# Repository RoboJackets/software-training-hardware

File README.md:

# software-training-hardware
Repository to contain all eagle files and any other electrical or mechanical files for the software training platform.

# Pin Mapping

| Pin | Type  In Actual | Type out actual | Notes |
|-|-|-|-|
| A0 | digital | PWM | |
| A1 | digital | PWM | |
| A2 | analog  | Na | |
| A3 | analog  | Na | |
| A4 | analog  | Na | |
| A5 | digital | PWM | |
| 13 | digital  | PWM | |
| 12 | Na  | Na | do not use |
| 27 | digital  | PWM | |
| 33 | analog   | PWM | |
| 15 | digital  | PWM | |
| 32 | analog   | PWM | |
| 14 | digital  | PWM | |

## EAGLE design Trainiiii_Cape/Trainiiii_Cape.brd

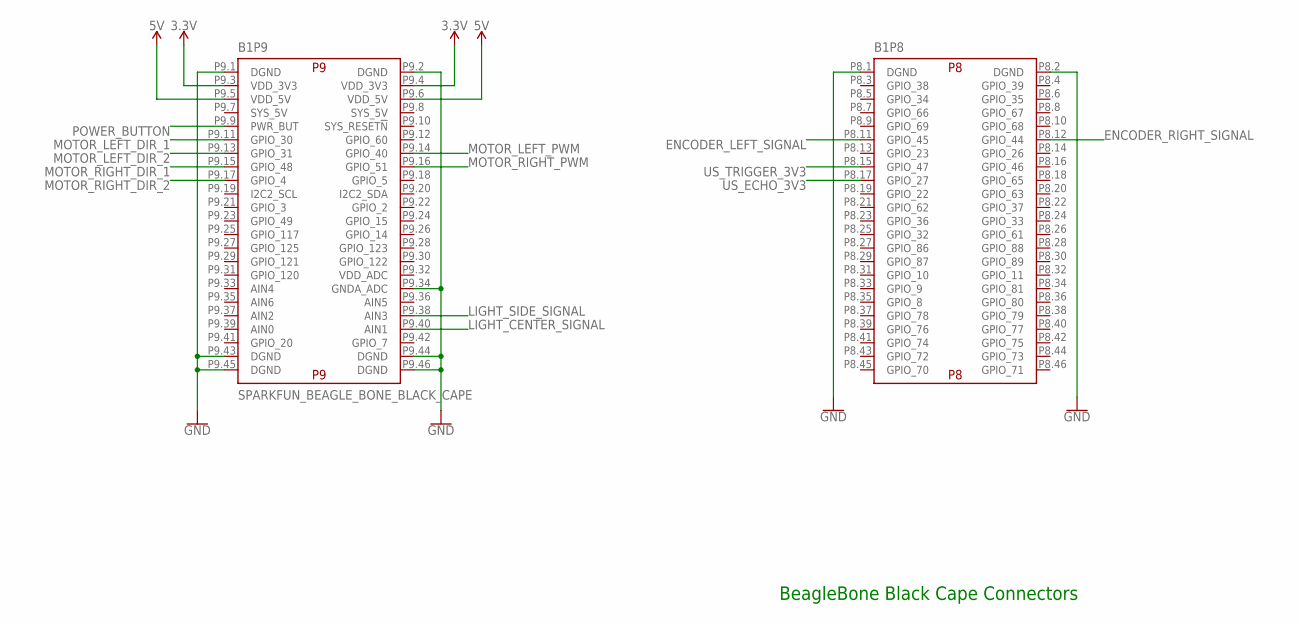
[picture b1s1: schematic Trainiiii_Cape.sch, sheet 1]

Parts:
B1: SPARKFUN_BEAGLE_BONE_BLACK_CAPE; BEAGLE_BONE_BLACK_CAPE

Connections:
3.3V: B1.P9.3 (VDD_3V3), B1.P9.4 (VDD_3V3); also elsewhere on the board
5V: B1.P9.5 (VDD_5V), B1.P9.6 (VDD_5V); also elsewhere on the board
ENCODER_LEFT_SIGNAL: B1.P8.11 (GPIO_45); also elsewhere on the board
ENCODER_RIGHT_SIGNAL: B1.P8.12 (GPIO_44); also elsewhere on the board
GND: B1.P8.1 (DGND), B1.P8.2 (DGND), B1.P9.1 (DGND), B1.P9.2 (DGND), B1.P9.34 (GNDA_ADC), B1.P9.43 (DGND), B1.P9.44 (DGND), B1.P9.45 (DGND), B1.P9.46 (DGND); also elsewhere on the board
LIGHT_CENTER_SIGNAL: B1.P9.40 (AIN1); also elsewhere on the board
LIGHT_SIDE_SIGNAL: B1.P9.38 (AIN3); also elsewhere on the board
MOTOR_LEFT_DIR_1: B1.P9.11 (GPIO_30); also elsewhere on the board
MOTOR_LEFT_DIR_2: B1.P9.13 (GPIO_31); also elsewhere on the board
MOTOR_LEFT_PWM: B1.P9.14 (GPIO_40); also elsewhere on the board
MOTOR_RIGHT_DIR_1: B1.P9.15 (GPIO_48); also elsewhere on the board
MOTOR_RIGHT_DIR_2: B1.P9.17 (GPIO_4); also elsewhere on the board
MOTOR_RIGHT_PWM: B1.P9.16 (GPIO_51); also elsewhere on the board
POWER_BUTTON: B1.P9.9 (PWR_BUT); also elsewhere on the board
US_ECHO_3V3: B1.P8.17 (GPIO_27); also elsewhere on the board
US_TRIGGER_3V3: B1.P8.15 (GPIO_47); also elsewhere on the board

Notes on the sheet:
BeagleBone Black Cape Connectors

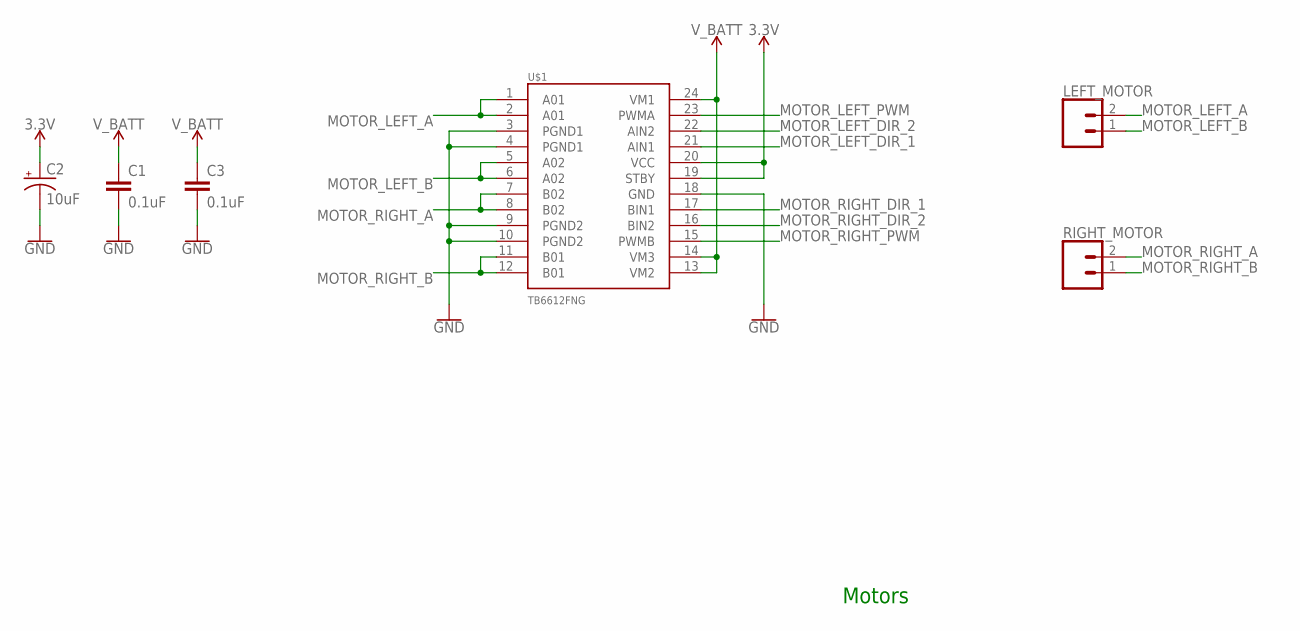
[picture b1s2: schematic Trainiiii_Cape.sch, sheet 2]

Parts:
C1, C3: 0.1uF; 0402
C2: 10uF; EIA3528
LEFT_MOTOR: CONN_02; 1X02
RIGHT_MOTOR: CONN_02; 1X02
U$1: TB6612FNG; SSOP24

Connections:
3.3V: C2.A (+), U$1.19 (STBY), U$1.20 (VCC); also elsewhere on the board
GND: C1.2, C2.C (-), C3.2, U$1.3 (PGND1), U$1.4 (PGND1), U$1.9 (PGND2), U$1.10 (PGND2), U$1.18 (GND); also elsewhere on the board
MOTOR_LEFT_A: LEFT_MOTOR.2, U$1.1 (A01), U$1.2 (A01)
MOTOR_LEFT_B: LEFT_MOTOR.1, U$1.5 (A02), U$1.6 (A02)
MOTOR_LEFT_DIR_1: U$1.21 (AIN1); also elsewhere on the board
MOTOR_LEFT_DIR_2: U$1.22 (AIN2); also elsewhere on the board
MOTOR_LEFT_PWM: U$1.23 (PWMA); also elsewhere on the board
MOTOR_RIGHT_A: RIGHT_MOTOR.2, U$1.7 (B02), U$1.8 (B02)
MOTOR_RIGHT_B: RIGHT_MOTOR.1, U$1.11 (B01), U$1.12 (B01)
MOTOR_RIGHT_DIR_1: U$1.17 (BIN1); also elsewhere on the board
MOTOR_RIGHT_DIR_2: U$1.16 (BIN2); also elsewhere on the board
MOTOR_RIGHT_PWM: U$1.15 (PWMB); also elsewhere on the board
V_BATT: C1.1, C3.1, U$1.13 (VM2), U$1.14 (VM3), U$1.24 (VM1); also elsewhere on the board

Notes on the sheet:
Motors

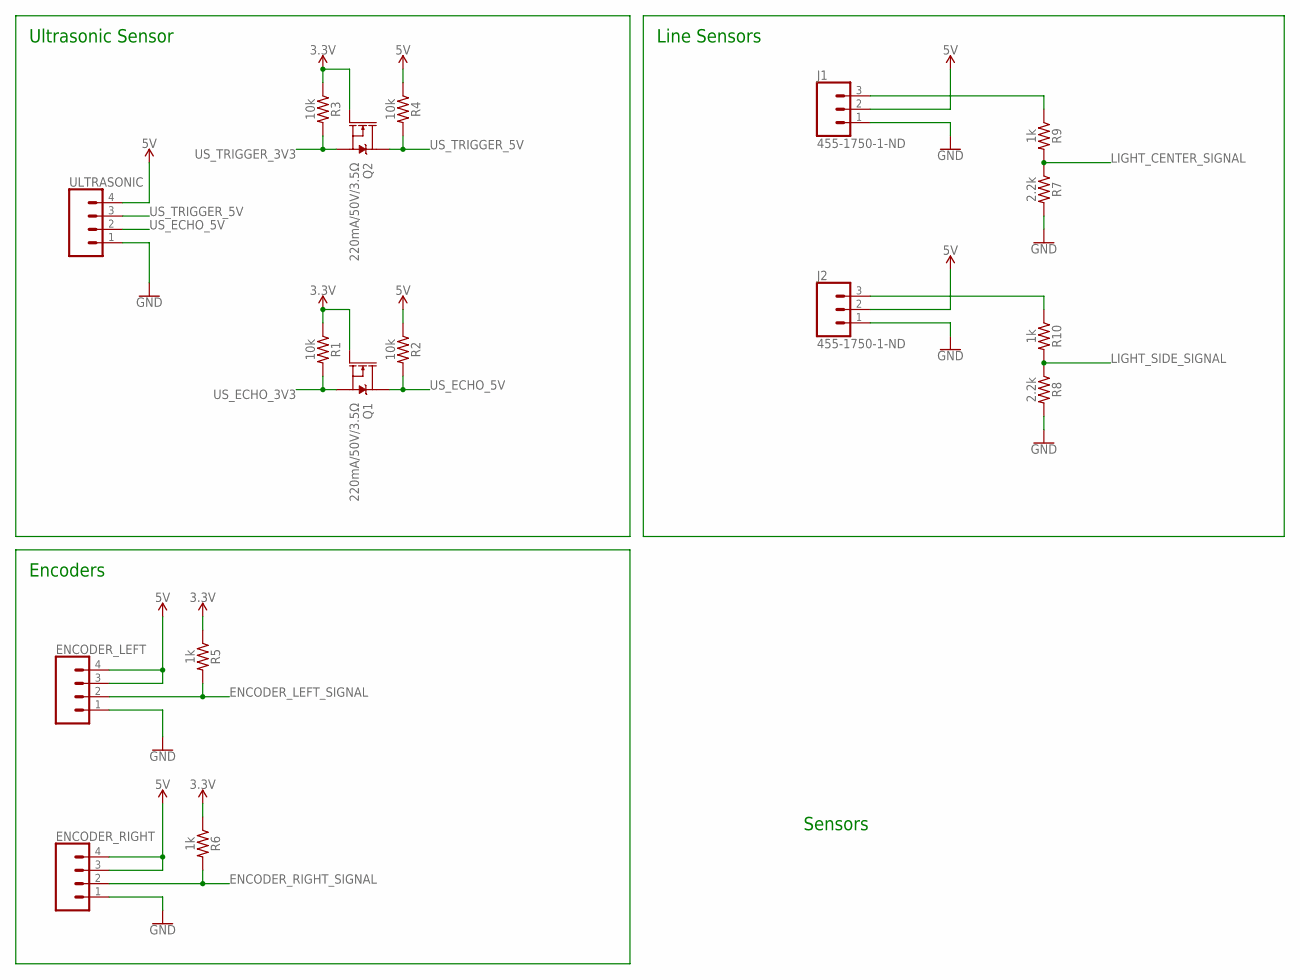
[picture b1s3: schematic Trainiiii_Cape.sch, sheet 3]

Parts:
ENCODER_LEFT: CONN_04PTH; 1X04
ENCODER_RIGHT: CONN_04PTH; 1X04
J1, J2: 455-1750-1-ND; 1X03
Q1, Q2: 220mA/50V/3.5Ω; SOT23-3
R1, R2, R3, R4: 10k; 0603
R5, R6, R9, R10: 1k; 0603
R7, R8: 2.2k; 0603
ULTRASONIC: CONN_04PTH; 1X04

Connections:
3.3V: Q1.1 (G), Q2.1 (G), R1.1, R3.1, R5.1, R6.1; also elsewhere on the board
5V: ENCODER_LEFT.3, ENCODER_LEFT.4, ENCODER_RIGHT.3, ENCODER_RIGHT.4, J1.2, J2.2, R2.1, R4.1, ULTRASONIC.4; also elsewhere on the board
ENCODER_LEFT_SIGNAL: ENCODER_LEFT.2, R5.2; also elsewhere on the board
ENCODER_RIGHT_SIGNAL: ENCODER_RIGHT.2, R6.2; also elsewhere on the board
GND: ENCODER_LEFT.1, ENCODER_RIGHT.1, J1.1, J2.1, R7.2, R8.2, ULTRASONIC.1; also elsewhere on the board
LIGHT_CENTER_SIGNAL: R7.1, R9.2; also elsewhere on the board
LIGHT_SIDE_SIGNAL: R8.1, R10.2; also elsewhere on the board
unnamed: J2.3, R10.1
unnamed: J1.3, R9.1
US_ECHO_3V3: Q1.2 (S), R1.2; also elsewhere on the board
US_ECHO_5V: Q1.3 (D), R2.2, ULTRASONIC.2
US_TRIGGER_3V3: Q2.2 (S), R3.2; also elsewhere on the board
US_TRIGGER_5V: Q2.3 (D), R4.2, ULTRASONIC.3

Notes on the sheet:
Ultrasonic Sensor
Line Sensors
Encoders
Sensors

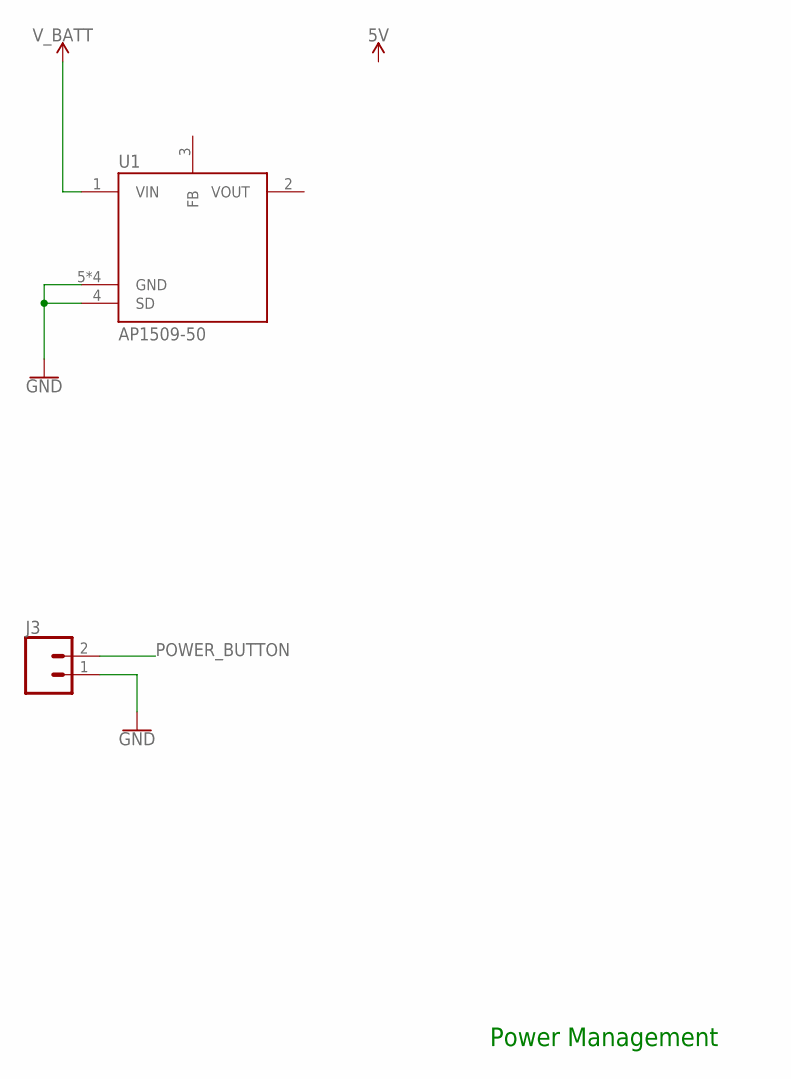
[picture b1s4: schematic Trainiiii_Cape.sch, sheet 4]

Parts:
J3: CONN_02; 1X02
U1: AP1509-50; SOIC-8

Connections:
GND: J3.1, U1.4 (SD), U1.5 (GND), U1.6 (GND), U1.7 (GND), U1.8 (GND); also elsewhere on the board
POWER_BUTTON: J3.2; also elsewhere on the board
V_BATT: U1.1 (VIN); also elsewhere on the board

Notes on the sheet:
Power Management

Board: 2 copper layers, 26 parts (0 on the bottom side), 25 nets, no tracks yet.

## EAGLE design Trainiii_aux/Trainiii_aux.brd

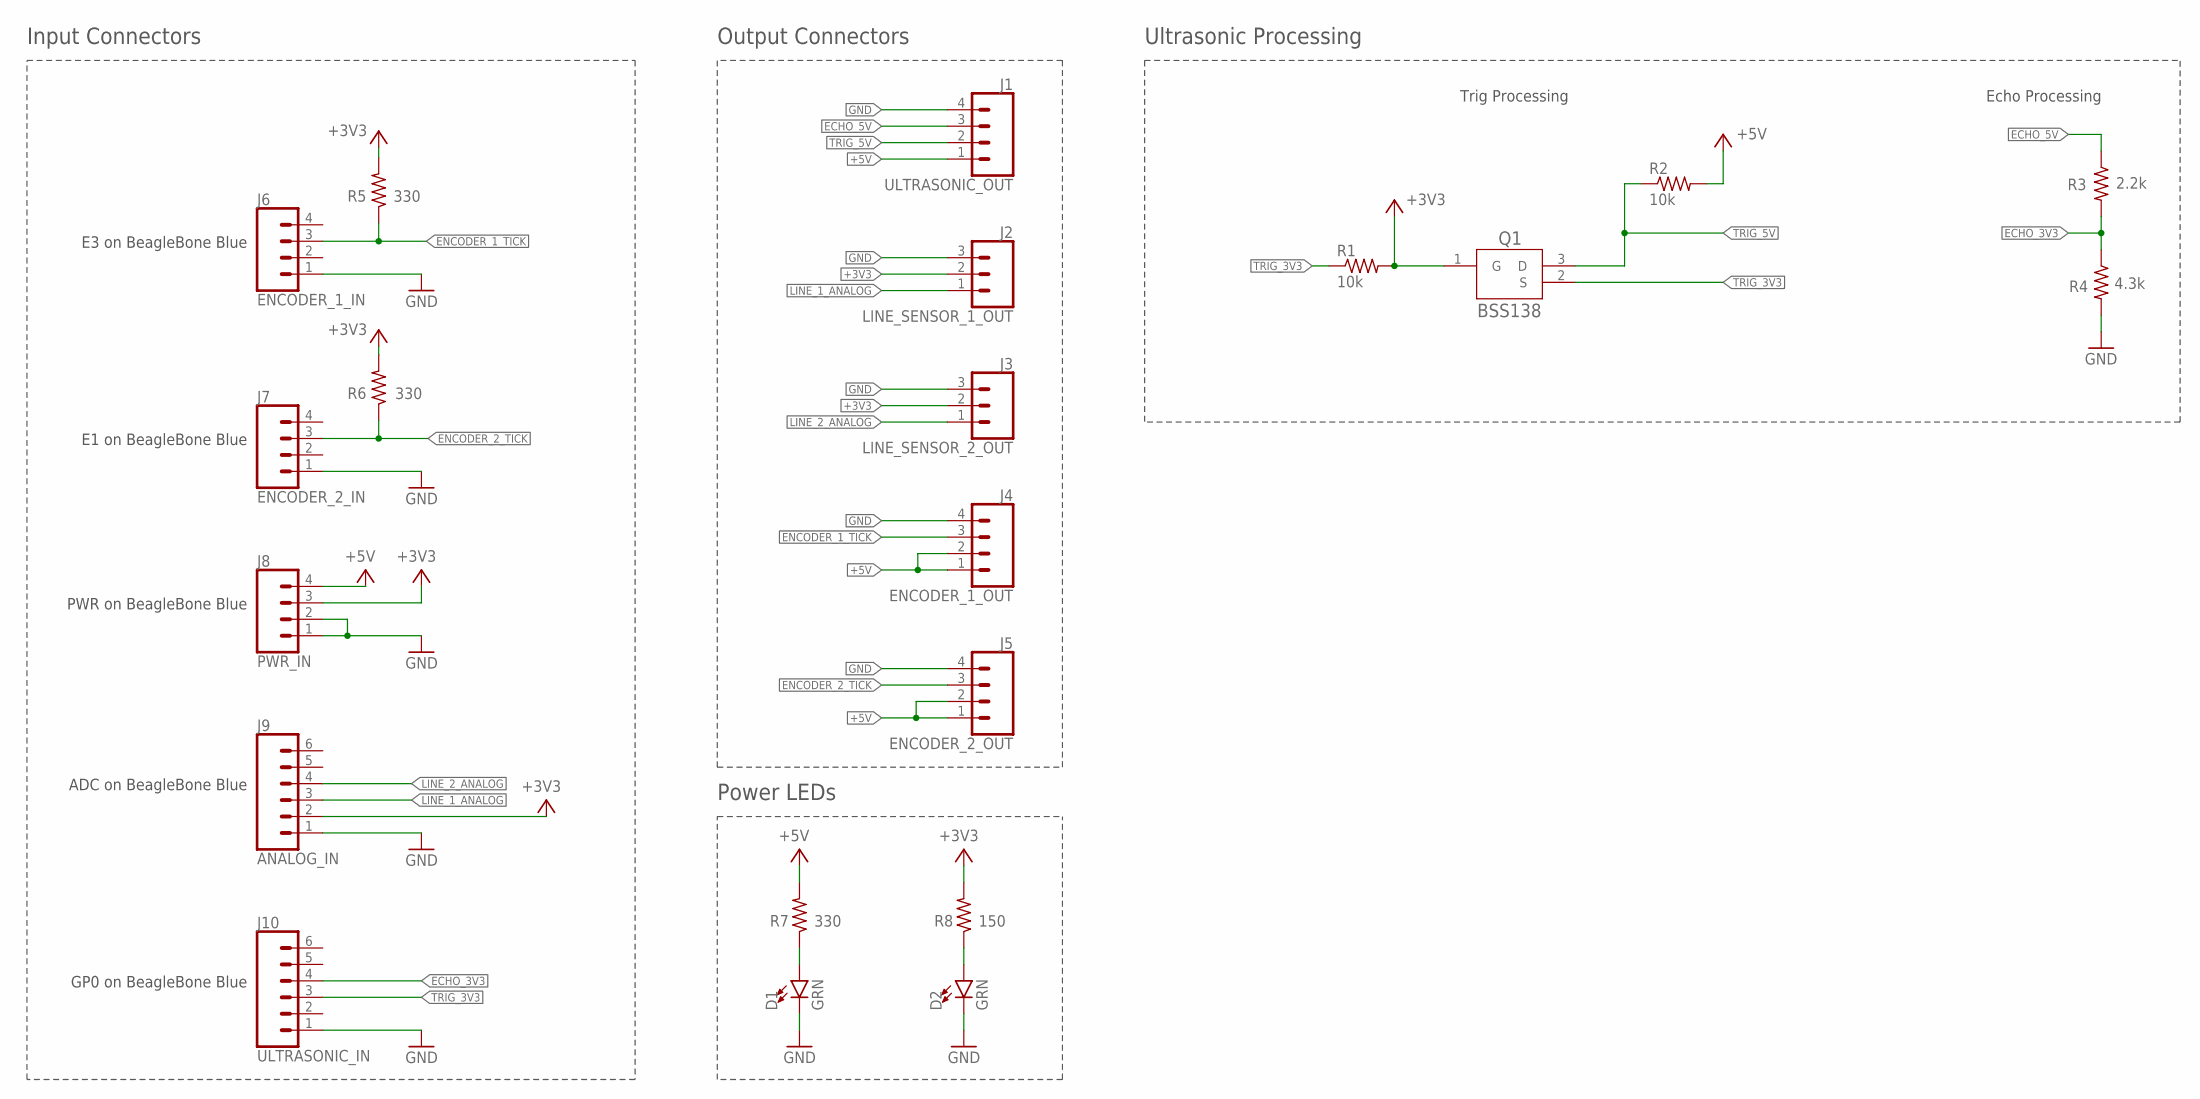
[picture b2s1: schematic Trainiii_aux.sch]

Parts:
D1, D2: GRN; LED-0603
J1: ULTRASONIC_OUT; 1X04
J2: LINE_SENSOR_1_OUT; 1X03
J3: LINE_SENSOR_2_OUT; 1X03
J4: ENCODER_1_OUT; 1X04
J5: ENCODER_2_OUT; 1X04
J6: ENCODER_1_IN; 1X04
J7: ENCODER_2_IN; 1X04
J8: PWR_IN; 1X04
J9: ANALOG_IN; 1X06
J10: ULTRASONIC_IN; 1X06
Q1: BSS138; SOT-23-3L
R1, R2: 10k; R0603
R3: 2.2k; R0603
R4: 4.3k; R0603
R5, R6, R7: 330; R0603
R8: 150; R0603

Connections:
3V3_LED: D2.A, R8.1
5V_LED: D1.A, R7.1
+3V3: J2.2, J3.2, J8.3, J9.2, Q1.1 (G), R1.2, R5.2, R6.2, R8.2
+5V: J1.1, J4.1, J4.2, J5.1, J5.2, J8.4, R2.2, R7.2
ECHO_3V3: J10.4, R3.2, R4.1
ECHO_5V: J1.3, R3.1
ENCODER_1_TICK: J4.3, J6.3, R5.1
ENCODER_2_TICK: J5.3, J7.3, R6.1
GND: D1.C, D2.C, J1.4, J2.3, J3.3, J4.4, J5.4, J6.1, J7.1, J8.1, J8.2, J9.1, J10.1, R4.2
LINE_1_ANALOG: J2.1, J9.3
LINE_2_ANALOG: J3.1, J9.4
TRIG_3V3: J10.3, Q1.2 (S), R1.1
TRIG_5V: J1.2, Q1.3 (D), R2.1

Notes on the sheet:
Output Connectors
Ultrasonic Processing
Trig Processing
Echo Processing
E1 on BeagleBone Blue
E3 on BeagleBone Blue
PWR on BeagleBone Blue
ADC on BeagleBone Blue
GP0 on BeagleBone Blue
Input Connectors
Power LEDs

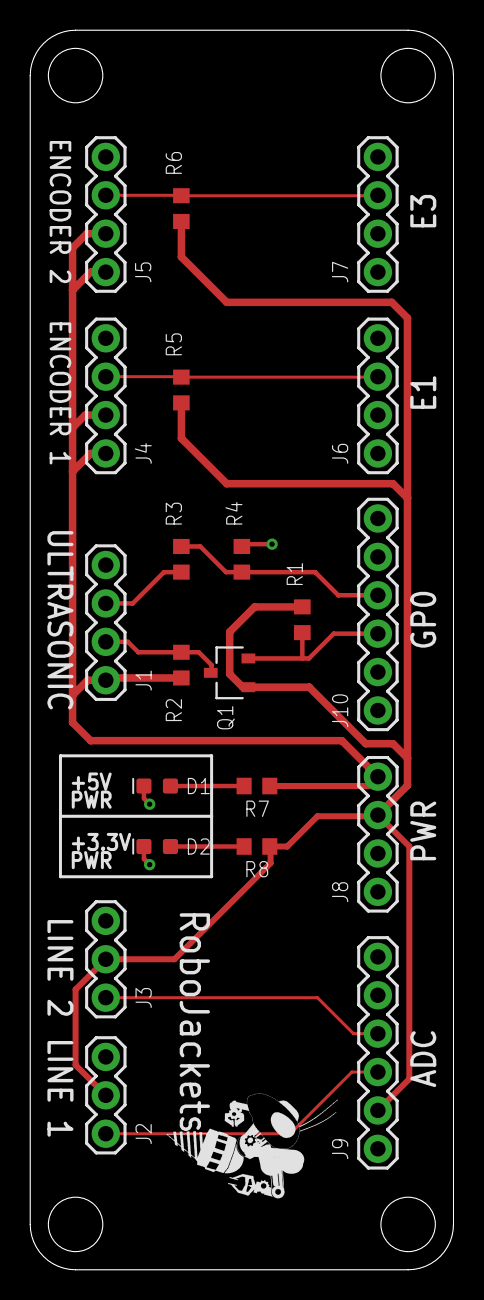
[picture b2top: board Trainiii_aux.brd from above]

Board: 2 copper layers, 28.0 x 82.0 mm, 22 parts (0 on the bottom side), 13 nets.

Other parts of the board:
U$1: ROBOBUZZ_0.6X

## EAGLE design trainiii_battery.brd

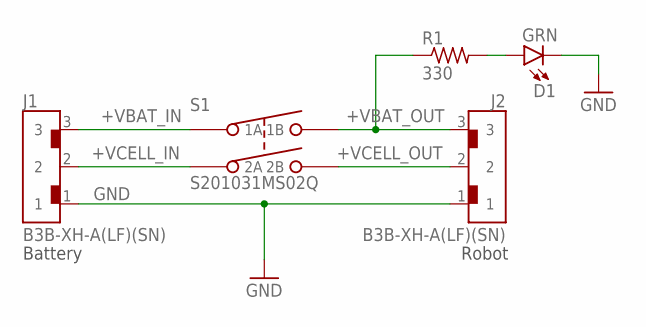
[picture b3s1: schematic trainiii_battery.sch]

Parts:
D1: GRN; LED-0603
J1, J2: B3B-XH-A(LF)(SN)
R1: 330; R0603
S1: S201031MS02Q; S201

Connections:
+VBAT_IN: J1.3, S1.1 (1A)
+VBAT_OUT: J2.3, R1.1, S1.2 (1B)
+VCELL_IN: J1.2, S1.4 (2A)
+VCELL_OUT: J2.2, S1.5 (2B)
GND: D1.C, J1.1, J2.1
LED_IN: D1.A, R1.2

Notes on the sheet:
Battery
Robot

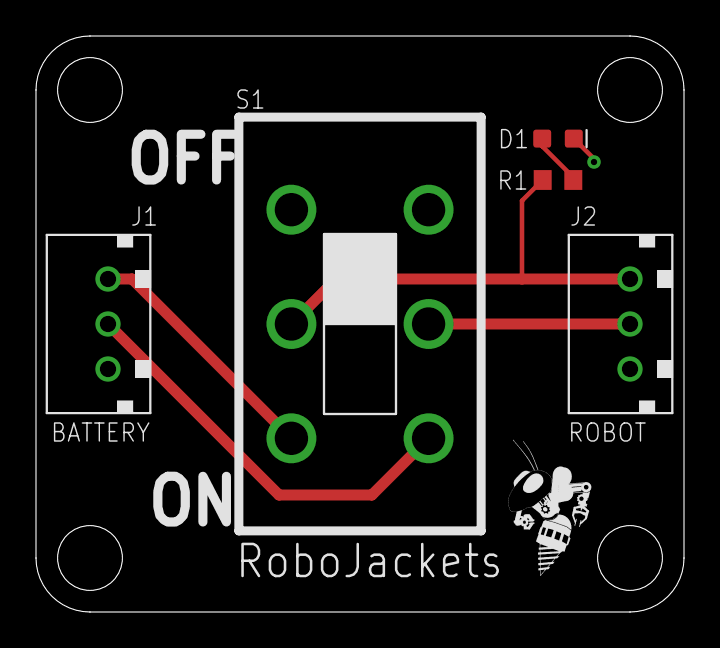
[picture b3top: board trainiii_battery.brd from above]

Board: 2 copper layers, 36.0 x 32.0 mm, 6 parts (0 on the bottom side), 6 nets.

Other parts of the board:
U$2: ROBOBUZZ_0.4X

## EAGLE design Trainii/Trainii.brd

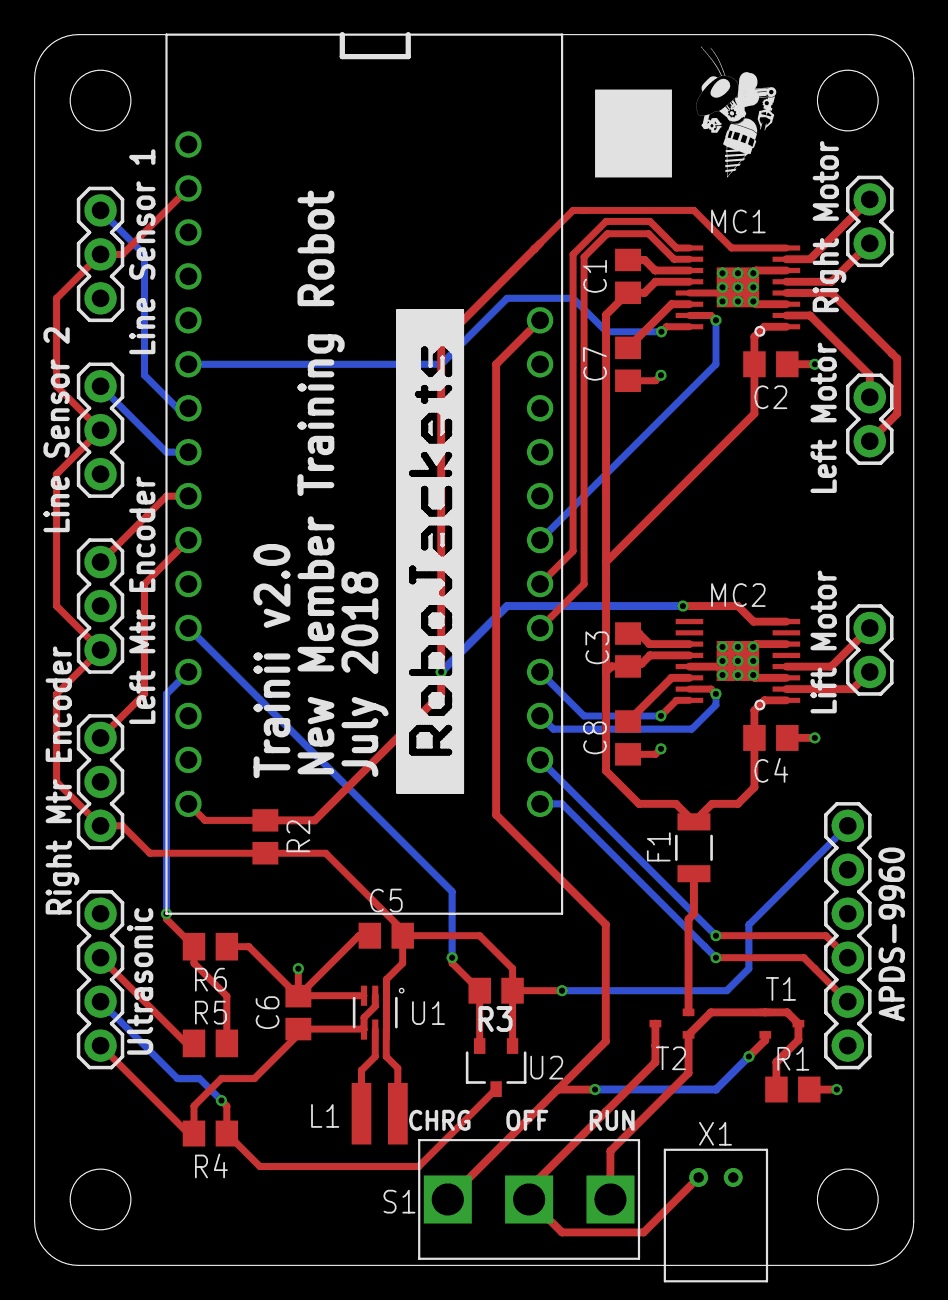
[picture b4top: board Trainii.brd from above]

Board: 2 copper layers, 50.8 x 71.1 mm, 36 parts (0 on the bottom side), 36 nets.

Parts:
C1, C3: 0.01uF; C0805
C2, C4: 10uF; C0805
C5, C6: 10uF 16V; C0805
C7, C8: 2.2uF; C0805
F1: 0ZCJ0100FF2E; 1206
J1: APDS-9960; 1X06
J2: Left Mtr Encoder; 1X03
J3: Right Mtr Encoder; 1X03
J4: Line Sensor 1; 1X03
J5: Line Sensor 2; 1X03
J6: Ultrasonic; 1X04
J7: Left Motor; 1X02
J8: Right Motor; 1X02
J9: Lift Motor; 1X02
L1: 4.7uH; VLS3012HBX
M1: ESP32
MC1, MC2: DRV8833; HTSSOP-16
R1, R2, R3, R4: 10kΩ; R0805
R5: 2k2Ω; M0805
R6: 4k3Ω; M0805
S1: 100SP3T
T1, T2: MCH3383SC-70FL; SOTFL65P210X90-3
U1: TPS61222DCKR; DCK6
U2: BSS138; SOT-23-3L
U$2: ROBOJACKETS
U$6: ROBOBUZZ_0.4X
X1: JST-PH2; JST-PH

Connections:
3V3: C5.1, J1.6, J2.1, J3.1, J4.2, J5.2, L1.1, M1.3V, R2.2, R3.1, U1.1, U1.6, U2.1
+5V: C6.1, J6.1, R4.1, U1.2, U1.4
ECHO_3V3: M1.MI, R5.2, R6.1
ECHO_5V: J6.3, R5.1
GND: C2.2, C4.2, C5.2, C6.2, C7.2, C8.2, J1.4, J2.2, J3.2, J4.1, J5.1, J6.4, M1.GND, MC1.3, MC1.6, MC1.13, MC1.17, MC2.3, MC2.6, MC2.13, MC2.17, R1.1, R6.2, U1.3, X1.1
LEFT_0: J7.1, MC1.2
LEFT_1: J7.2, MC1.4
LEFT_A: M1.A1, MC1.16
LEFT_B: M1.A10, MC1.15
LIFT_0: J9.1, MC2.2
LIFT_1: J9.2, MC2.4
LIFT_A: M1.A7, MC2.16
LIFT_B: M1.A6, MC2.15
LINE_OUT_1: J4.3, M1.A2
LINE_OUT_2: J5.3, M1.A3
MOTOR_FAULT: M1.21, MC1.8, MC2.8, R2.1
unnamed: L1.2, U1.5
unnamed: R1.2, S1.3, T1.1, T1.3, T2.1
unnamed: C8.1, MC2.14
unnamed: C1.1, MC1.11
unnamed: C7.1, MC1.14
unnamed: C3.1, MC2.11
RIGHT_0: J8.1, MC1.7
RIGHT_1: J8.2, MC1.5
RIGHT_A: M1.A9, MC1.9
RIGHT_B: M1.A8, MC1.10
SCL: J1.3, M1.22
SDA: J1.2, M1.23
TICK_LEFT: J2.3, M1.A4
TICK_RIGHT: J3.3, M1.A5
TRIG_3V3: M1.MO, R3.2, U2.2
TRIG_5V: J6.2, R4.2, U2.3
VBAT: S1.2, T2.3, X1.2
VBAT_HUZZAH: M1.BAT, S1.1, T1.2
VBAT_MOTOR: F1.1, T2.2
VBAT_MOTOR_FUSE: C1.2, C2.1, C3.2, C4.1, F1.2, MC1.1, MC1.12, MC2.1, MC2.12

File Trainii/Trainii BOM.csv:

"Part";"Value";"Device";"Package";"Description";"MANUFACTURER_PART_NUMBER";"PROD_ID";"SPICEPREFIX";"VENDOR";
"C1";"0.01uF";"C-USC0805";"C0805";"CAPACITOR, American symbol";"";"";"C";"";
"C2";"10uF";"C-USC0805";"C0805";"CAPACITOR, American symbol";"";"";"C";"";
"C3";"0.01uF";"C-USC0805";"C0805";"CAPACITOR, American symbol";"";"";"C";"";
"C4";"10uF";"C-USC0805";"C0805";"CAPACITOR, American symbol";"";"";"C";"";
"C5";"10uF 16V";"C-USC0805";"C0805";"CAPACITOR, American symbol";"";"";"C";"";
"C6";"10uF 16V";"C-USC0805";"C0805";"CAPACITOR, American symbol";"";"";"C";"";
"C7";"2.2uF";"C-USC0805";"C0805";"CAPACITOR, American symbol";"";"";"C";"";
"C8";"2.2uF";"C-USC0805";"C0805";"CAPACITOR, American symbol";"";"";"C";"";
"F1";"0ZCJ0100FF2E";"0ZCJ0100FF2E";"1206";"";"";"";"";"";
"J1";"APDS-9960";"CONN_06SILK_FEMALE_PTH";"1X06";"Multi connection point. Often used as Generic Header-pin footprint for 0.1 inch spaced/style header connections";"";"CONN-08437";"";"";
"J2";"Left Mtr Encoder";"CONN_03";"1X03";"Multi connection point. Often used as Generic Header-pin footprint for 0.1 inch spaced/style header connections";"";"";"";"";
"J3";"Right Mtr Encoder";"CONN_03";"1X03";"Multi connection point. Often used as Generic Header-pin footprint for 0.1 inch spaced/style header connections";"";"";"";"";
"J4";"Line Sensor 1";"CONN_03";"1X03";"Multi connection point. Often used as Generic Header-pin footprint for 0.1 inch spaced/style header connections";"";"";"";"";
"J5";"Line Sensor 2";"CONN_03";"1X03";"Multi connection point. Often used as Generic Header-pin footprint for 0.1 inch spaced/style header connections";"";"";"";"";
"J6";"Ultrasonic";"CONN_04";"1X04";"Multi connection point. Often used as Generic Header-pin footprint for 0.1 inch spaced/style header connections";"";"CONN-09696";"";"";
"J7";"Left Motor";"CONN_02";"1X02";"Multi connection point. Often used as Generic Header-pin footprint for 0.1 inch spaced/style header connections";"";"";"";"";
"J8";"Right Motor";"CONN_02";"1X02";"Multi connection point. Often used as Generic Header-pin footprint for 0.1 inch spaced/style header connections";"";"";"";"";
"J9";"Lift Motor";"CONN_02";"1X02";"Multi connection point. Often used as Generic Header-pin footprint for 0.1 inch spaced/style header connections";"";"";"";"";
"L1";"4.7uH";"VLS3012HBX";"VLS3012HBX";"";"";"";"";"";
"M1";"ESP32";"ESP32";"ESP32";"";"";"";"";"";
"MC1";"DRV8833";"DRV8833";"HTSSOP-16";"";"";"";"";"";
"MC2";"DRV8833";"DRV8833";"HTSSOP-16";"";"";"";"";"";
"R1";"10kΩ";"R-US_R0805";"R0805";"RESISTOR, American symbol";"";"";"R";"";
"R2";"10kΩ";"R-US_R0805";"R0805";"RESISTOR, American symbol";"";"";"R";"";
"R3";"10kΩ";"R-US_R0805";"R0805";"RESISTOR, American symbol";"";"";"R";"";
"R4";"10kΩ";"R-US_R0805";"R0805";"RESISTOR, American symbol";"";"";"R";"";
"R5";"47Ω";"R-US_M0805";"M0805";"RESISTOR, American symbol";"";"";"R";"";
"R6";"91Ω";"R-US_M0805";"M0805";"RESISTOR, American symbol";"";"";"R";"";
"S1";"100SP3T";"100SP3T";"100SP3T";"";"";"";"";"";
"T1";"MCH3383SC-70FL";"MCH3383SC-70FL";"SOTFL65P210X90-3";"";"";"";"";"";
"T2";"MCH3383SC-70FL";"MCH3383SC-70FL";"SOTFL65P210X90-3";"";"";"";"";"";
"T3";"MCH3383SC-70FL";"MCH3383SC-70FL";"SOTFL65P210X90-3";"";"";"";"";"";
"U1";"TPS61222DCKR";"TPS61222DCKR";"DCK6";"";"TPS61222DCKR";"";"";"Texas Instruments";
"U2";"BSS138";"BSS138";"SOT-23-3L";"";"BSS138";"";"";"Fairchild Semiconductor";
"X1";"JST-PH2";"JST-PH2";"JST-PH";"";"";"";"";"";

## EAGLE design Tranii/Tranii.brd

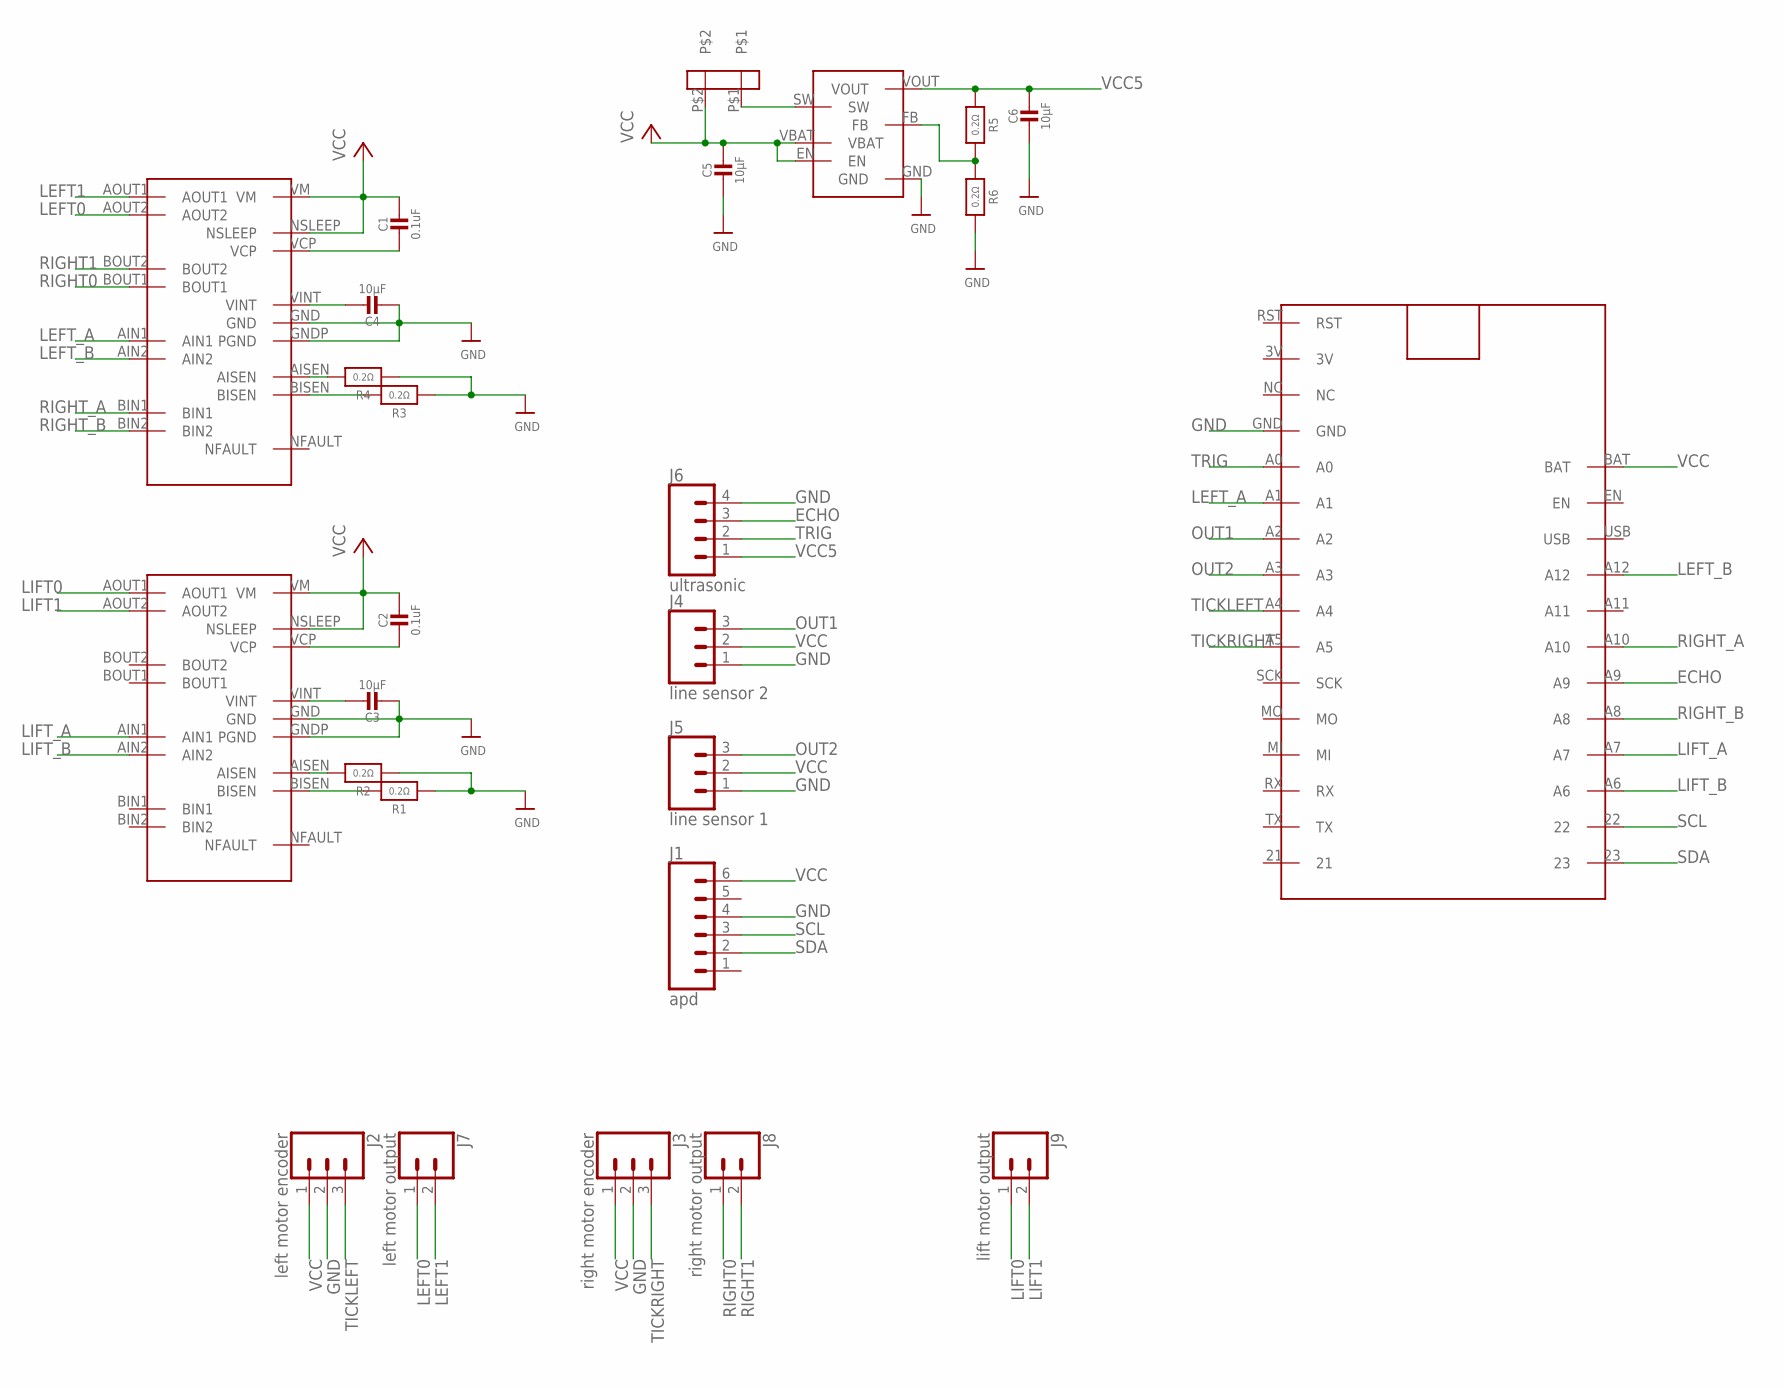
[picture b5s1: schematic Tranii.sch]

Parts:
C1, C2: 0.1uF; 0805-NO
C3, C4, C5, C6: 10µF; 0805-NO
J1: apd; 1X06
J2: left motor encoder; 1X03
J3: right motor encoder; 1X03
J4: line sensor 2; 1X03
J5: line sensor 1; 1X03
J6: ultrasonic; 1X04
J7: left motor output; 1X02
J8: right motor output; 1X02
J9: lift motor output; 1X02
R1, R2, R3, R4, R5, R6: 0.2Ω; _1206
U$1, U$2: DRV8833
U$6: ESP32
U$8: LPV61220; TLV61220
U$11: VLS3012HBX

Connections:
ECHO: J6.3, U$6.A9
GND: C3.2, C4.2, C5.2, C6.2, J1.4, J2.2, J3.2, J4.1, J5.1, J6.4, R1.1, R2.1, R3.1, R4.1, R6.2, U$1.GND, U$1.GNDP (PGND), U$2.GND, U$2.GNDP (PGND), U$6.GND, U$8.GND
LEFT0: J7.1, U$1.AOUT2
LEFT1: J7.2, U$1.AOUT1
LEFT_A: U$1.AIN1, U$6.A1
LEFT_B: U$1.AIN2, U$6.A12
LIFT0: J9.1, U$2.AOUT1
LIFT1: J9.2, U$2.AOUT2
LIFT_A: U$2.AIN1, U$6.A7
LIFT_B: U$2.AIN2, U$6.A6
unnamed: R5.2, R6.1, U$8.FB
unnamed: U$8.SW, U$11.P$1
unnamed: C2.2, U$2.VCP
unnamed: R1.2, U$2.BISEN
unnamed: C3.1, U$2.VINT
unnamed: R2.2, U$2.AISEN
unnamed: C1.2, U$1.VCP
unnamed: C4.1, U$1.VINT
unnamed: R3.2, U$1.BISEN
unnamed: R4.2, U$1.AISEN
OUT1: J4.3, U$6.A2
OUT2: J5.3, U$6.A3
RIGHT0: J8.1, U$1.BOUT1
RIGHT1: J8.2, U$1.BOUT2
RIGHT_A: U$1.BIN1, U$6.A10
RIGHT_B: U$1.BIN2, U$6.A8
SCL: J1.3, U$6.22
SDA: J1.2, U$6.23
TICKLEFT: J2.3, U$6.A4
TICKRIGHT: J3.3, U$6.A5
TRIG: J6.2, U$6.A0
VCC: C1.1, C2.1, C5.1, J1.6, J2.1, J3.1, J4.2, J5.2, U$1.NSLEEP, U$1.VM, U$2.NSLEEP, U$2.VM, U$6.BAT, U$8.EN, U$8.VBAT, U$11.P$2
VCC5: C6.1, J6.1, R5.1, U$8.VOUT

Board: 2 copper layers, 26 parts (0 on the bottom side), 33 nets, no tracks yet.

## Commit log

2018-05-15 brought gitignore in line with RC gitignore
2018-05-15 inital library commit
2018-05-16 corrected issues in library and start creating the schematic
2018-05-16 finished pin mapping
2018-05-17 cleaned up schematic
2018-05-18 finished schematic
2018-05-18 renamed files to fix typo
2018-05-18 Changed a few parts, corrected small wiring connections, routed board
2018-05-18 Ran design rule checks
2018-05-19 fixed readme
2018-05-19 Squeezes board to 2in width.
    Re-layout to try to fit board into last draft of the mechanical CAD.
2018-05-19 Fixes spacing between ECHO3.3 and R8
2018-05-19 Fixes location of J9
    It was slightly off of the 0.1" grid I tried to fit all of the connectors to.
2018-05-19 Fixes header spacing for the Huzzah ESP32 in Trainii.lbr
2018-05-20 Realigned some routing to pads on ICs
2018-05-25 Added fuse, changed power source, fixed some routing widths
2018-05-28 Prepared gerber and BOM for order
2018-07-11 Updated Library, began fixing schematic
2018-07-11 Continued library update and finished schematic driver correction
2018-07-18 Added new battery connector
2018-07-23 edited schematic to include 3-position switch to select charging, running, or off
2018-07-26 Updated Libraries, corrected component placement
2018-07-26 Initial component placement before routing
2018-07-28 Initial routing
2018-07-29 Finished routing, exported images
2018-07-29 Added Switch Labels
2018-07-30 fixed table rendering
2018-07-31 Design Review Changes
2018-07-31 A E S T H E T I C S
2018-07-31 Moved robobuzz
2018-07-31 Added place for numbering, updated images and bom
2018-08-03 Increase resistance to reduce current
2018-08-03 Adjusted small routes
2018-08-07 Removed additional transistor to allow for charging to work correctly
2018-08-07 Added gerbers
2018-08-07 Corrected gerber
2019-07-07 Initial commit of battery switch board
2019-07-07 Added status LED, cleaned up board layout
2019-07-10 Final Order v1.0
2019-08-07 Initial Restructure and Trainiii Aux board design
2019-08-07 Finish initial version of Aux board
2019-08-07 Flipped location of RoboJackets, RoboBuzz
2019-08-13 Created Trainiii Aux gerber
2020-01-30 Removed Traini v2 files
2020-05-17 Adds Trainiiii Cape
    Starting the V4 design by capturing my breadboard design
2020-05-20 Organization and pin changes.
    Moved ultrasonic lines to pins that don't interfere with BBB boot sequence. Began organizing things into sheets!

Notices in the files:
parts and their libraries:
SparkFun-Connectors: Licensing: Creative Commons ShareAlike 4.0 International - https://creativecommons.org/licenses/by-sa/4.0
